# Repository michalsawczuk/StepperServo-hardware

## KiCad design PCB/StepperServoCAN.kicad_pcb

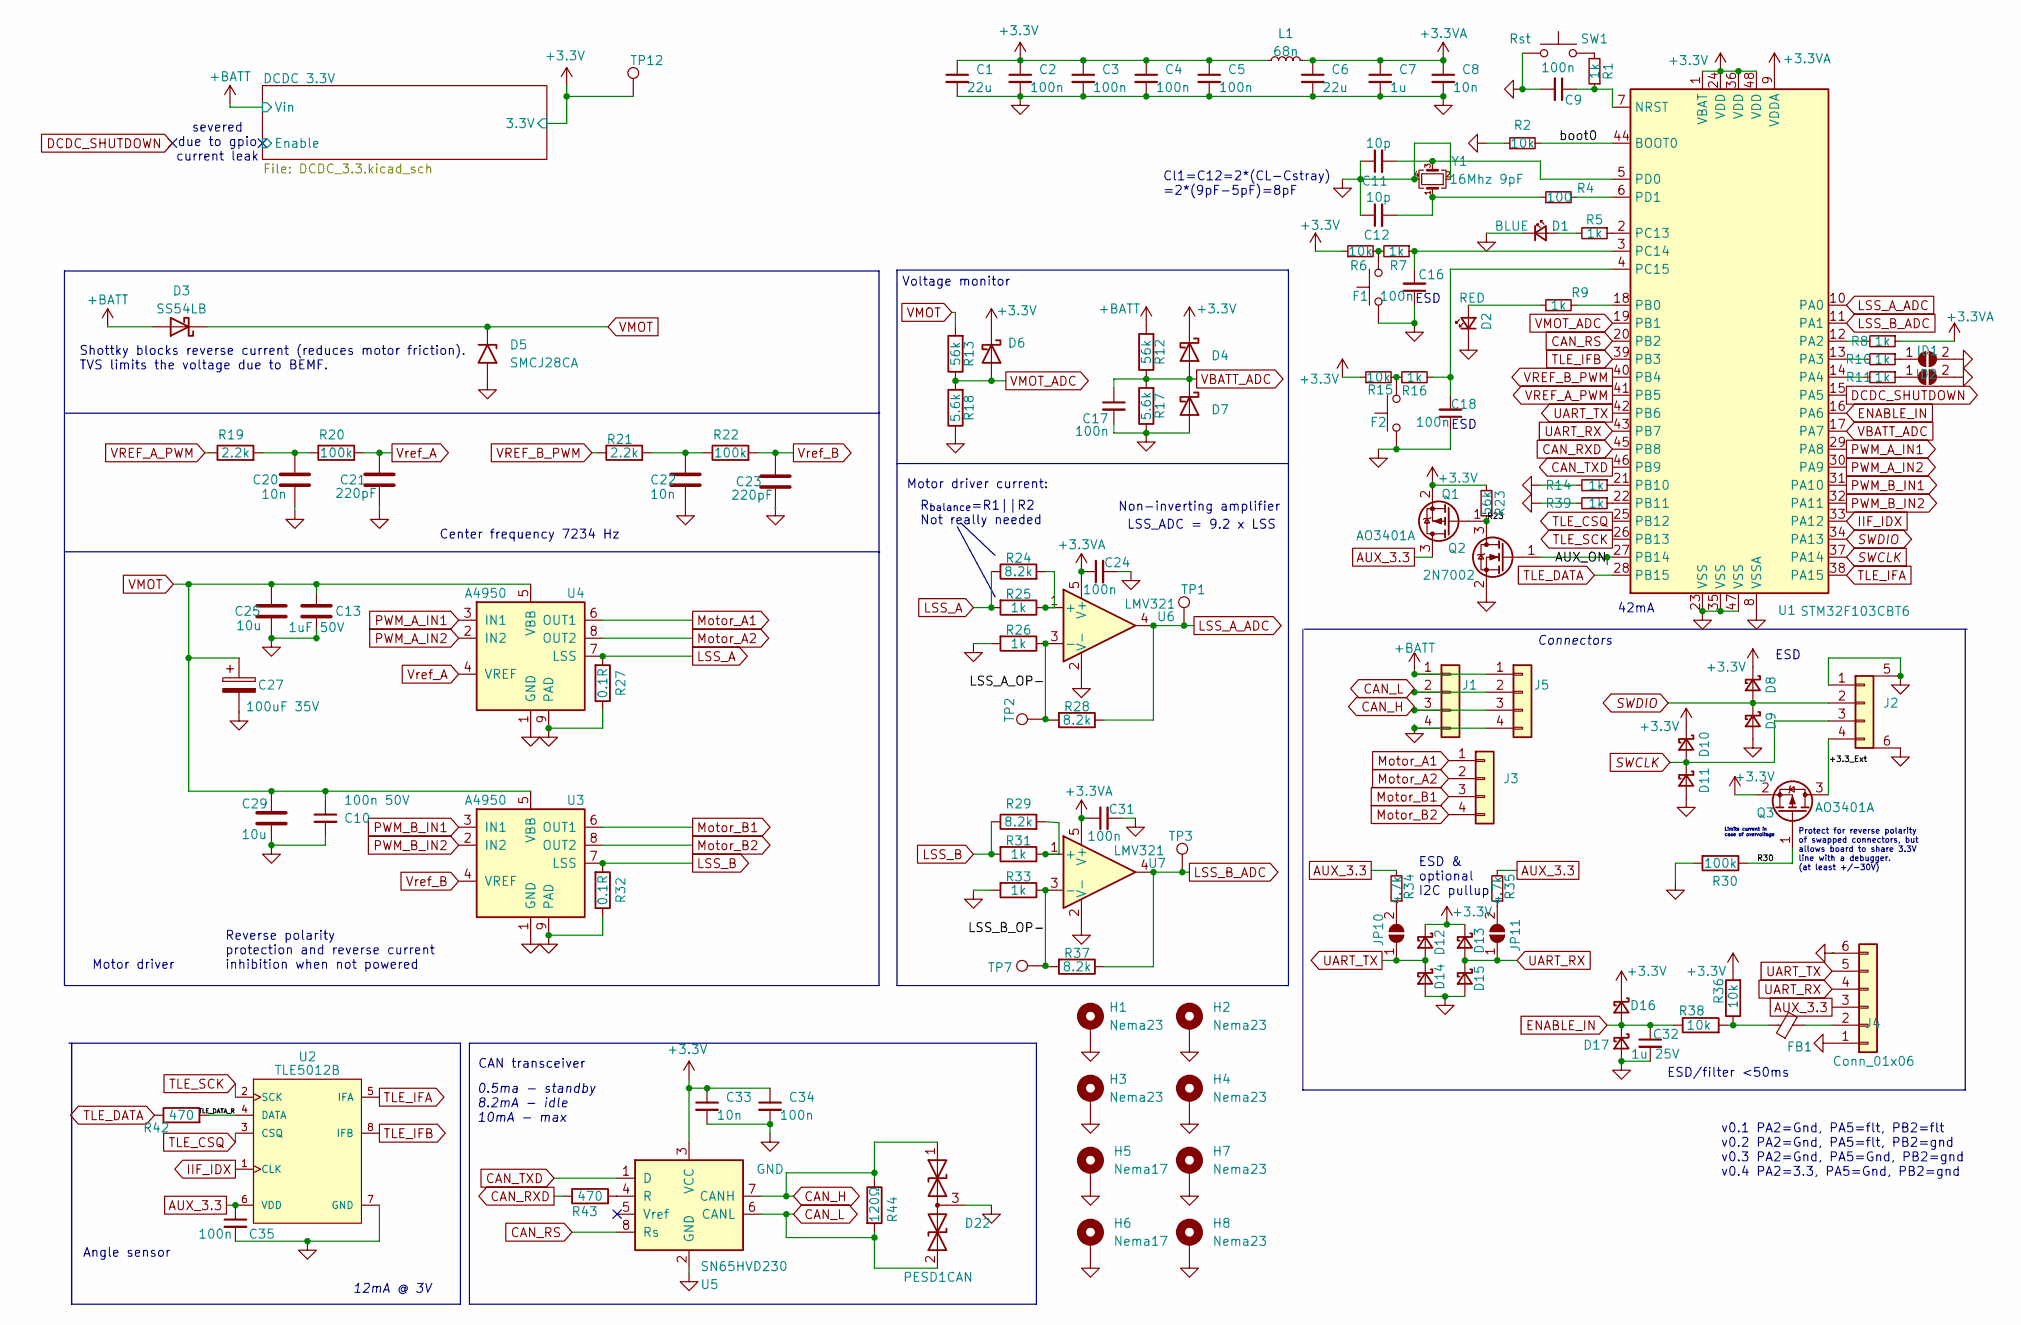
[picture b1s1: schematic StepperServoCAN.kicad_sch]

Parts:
C1, C6: 22u; C_0603_1608Metric; LCSC C59461
C2, C3, C4, C5, C9, C16, C17, C18, C24, C31, C34, C35: 100n; C_0402_1005Metric; LCSC C1525
C7: 1u; C_0402_1005Metric; LCSC C52923
C8, C20, C22, C33: 10n; C_0402_1005Metric; LCSC C15195
C10: 100n 50V; C_0402_1005Metric; LCSC C307331
C11, C12: 10p; C_0402_1005Metric; LCSC C32949
C13: 1uF 50V; C_0805_2012Metric; LCSC C28323
C21, C23: 220pF; C_0402_1005Metric; LCSC C1530
C25, C29: 10u; C_1206_3216Metric; LCSC C13585
C27: 100uF 35V; CP_Elec_6.3x5.7; LCSC C249982
C32: 1u 25V; C_0402_1005Metric; LCSC C52923
D1: BLUE; LED_0603_1608Metric; LCSC C2986058
D2: RED; LED_0603_1608Metric; LCSC C2286
D3: SS54LB; D_SMA; LCSC C7450527
D4, D6, D7, D8, D9, D10, D11, D12, D13, D14, D15, D16, D17: 1N5819WS; D_SOD-323; LCSC C191023
D5: SMCJ28CA; D_SMC; LCSC C19077606
D22: PESD1CAN; SOT-23; LCSC C152727
F1, F2: Fcn>; SW_SPST_TL3342; LCSC C318884
FB1: FerriteBead 200mA; L_0805_2012Metric; LCSC C1017
H1, H2, H3, H4, H7, H8: Nema23; MountingHole_3.2mm_M3_ISO14580_Pad_TopOnly
H5, H6: Nema17; MountingHole_3.2mm_M3_ISO14580_Pad_TopOnly
ID1, ID2: Jumper; SolderJumper-2_P1.3mm_Open_TrianglePad1.0x1.5mm
J1, J5: CAR; JST_XH_B4B-XH-A_1x04_P2.50mm_Vertical; LCSC C161861
J2: Debug; JST-S4B-XH-SM4-TB; LCSC C161861
J3: Motor; JST_XH_B4B-XH-A_1x04_P2.50mm_Vertical; LCSC C161861
J4: Conn_01x06; TerminalBlock_TE_282834-6_1x06_P2.54mm_Horizontal
JP10, JP11: I2C_PU; SolderJumper-2_P1.3mm_Open_RoundedPad1.0x1.5mm
L1: 68n; L_0603_1608Metric; LCSC C13415
Q1, Q3: AO3401A; SOT-23; LCSC C15127
Q2: 2N7002; SOT-23; LCSC C8545
R1, R5, R7, R8, R9, R10, R11, R14, R16, R25, R26, R31, R33, R39: 1k; R_0402_1005Metric; LCSC C11702
R2, R6, R15, R36, R38: 10k; R_0402_1005Metric; LCSC C25744
R4: 100; R_0402_1005Metric; LCSC C25076
R12, R13, R23: 56k; R_0402_1005Metric; LCSC C25796
R17, R18: 5.6k; R_0402_1005Metric; LCSC C25908
R19, R21: 2.2k; R_0402_1005Metric; LCSC C25879
R20, R22, R30: 100k; R_0402_1005Metric; LCSC C25741
R24, R28, R29, R37: 8.2k; R_0402_1005Metric; LCSC C25924
R27, R32: 0.1R; R_1206_3216Metric_Pad1.30x1.75mm_HandSolder; LCSC C201308
R34, R35: 4.7k; R_0805_2012Metric_Pad1.20x1.40mm_HandSolder; LCSC C17673
R42, R43: 470; R_0603_1608Metric; LCSC C23179
R44: 120Ω; R_1206_3216Metric_Pad1.30x1.75mm_HandSolder; LCSC C17909
SW1: Rst; SW_SPST_TL3342; LCSC C318884
TP1, TP2, TP3, TP7, TP12: Pad; TestPoint_Pad_D1.0mm
U1: STM32F103CBT6; LQFP-48_7x7mm_P0.5mm; LCSC C8734
U2: TLE5012B; Infineon-TLE5012-Level_A; LCSC C123083
U3, U4: A4950; SOIC-8-1EP_3.9x4.9mm_P1.27mm_EP2.41x3.3mm_ThermalVias; LCSC C82404
U5: SN65HVD230; SOIC-8_3.9x4.9mm_P1.27mm; LCSC C12084
U6, U7: LMV321; SOT-23-5; LCSC C7972
Y1: 16Mhz 9pF; Crystal_SMD_3225-4Pin_3.2x2.5mm; LCSC C13738

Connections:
+3.3V: C1.1, C2.1, C3.1, C4.1, C5.1, C33.1, C34.1, D4.1 (K), D6.1 (K), D8.1 (K), D10.1 (K), D12.1 (K), D13.1 (K), D16.1 (K), L1.1, Q1.2 (S), Q3.2 (S), R6.1, R15.1, R23.2, R36.2, TP12.1, U1.1 (VBAT), U1.24 (VDD), U1.36 (VDD), U1.48 (VDD), U5.3 (VCC); also elsewhere on the board
+3.3VA: C6.1, C7.1, C8.1, C24.1, C31.1, L1.2, R8.1, U1.9 (VDDA), U6.5 (V+), U7.5 (V+)
+BATT: D3.2 (A), J1.1, J5.1, R12.2; also elsewhere on the board
/+3.3_Ext: J2.4, Q3.3 (D)
/AUX_ON: Q2.1 (G), U1.27 (PB14)
/LSS_A_OP-: R26.1, R28.2, TP2.1, U6.3 (-)
/LSS_B_OP-: R33.1, R37.2, TP7.1, U7.3 (-)
/R23: Q1.1 (G), Q2.3 (D), R23.1
/R30: Q3.1 (G), R30.1
/TLE_DATA_R: R42.2, U2.4 (DATA)
/boot0: R2.2, U1.44 (BOOT0)
AUX_3.3: C35.1, J4.3, Q1.3 (D), R34.2, R35.2, U2.6 (VDD)
CAN_H: D22.1 (A1), J1.3, J5.3, R44.1, U5.7 (CANH)
CAN_L: D22.2 (A2), J1.2, J5.2, R44.2, U5.6 (CANL)
CAN_RS: U1.20 (PB2), U5.8 (Rs)
CAN_RXD: R43.1, U1.45 (PB8)
CAN_TXD: U1.46 (PB9), U5.1 (D)
DCDC_SHUTDOWN: U1.15 (PA5)
ENABLE_IN: C32.1, D16.2 (A), D17.1 (K), R38.1, U1.16 (PA6)
GND: C1.2, C2.2, C3.2, C4.2, C5.2, C6.2, C7.2, C8.2, C9.2, C10.2, C11.1, C12.1, C13.2, C16.1, C17.2, C18.1, C20.2, C21.2, C22.2, C23.2, C24.2, C25.2, C27.2, C29.2, C31.2, C32.2, C33.2, C34.2, C35.2, D1.1 (K), D2.1 (K), D5.2 (A2), D7.2 (A), D9.2 (A), D11.2 (A), D14.2 (A), D15.2 (A), D17.2 (A), D22.3 (common), F1.2, F2.2, H1.1, H2.1, H3.1, H4.1, H5.1, H6.1, H7.1, H8.1, ID1.2 (B), ID2.2 (B), J1.4, J2.1, J2.5 (Mount), J2.6 (Mount), J4.1, J4.6, J5.4, Q2.2 (S), R2.1, R14.2, R17.1, R18.1, R26.2, R27.1, R30.2, R32.1, R33.2, R39.2, SW1.1, U1.8 (VSSA), U1.23 (VSS), U1.35 (VSS), U1.47 (VSS), U2.7 (GND), U3.1 (GND), U3.9 (PAD), U4.1 (GND), U4.9 (PAD), U5.2 (GND), U6.2 (V-), U7.2 (V-), Y1.2, Y1.4; also elsewhere on the board
IIF_IDX: U1.33 (PA12), U2.1 (CLK)
LSS_A: R24.1, R25.2, R27.2, U4.7 (LSS)
LSS_A_ADC: R28.1, TP1.1, U1.10 (PA0), U6.4
LSS_B: R29.1, R31.2, R32.2, U3.7 (LSS)
LSS_B_ADC: R37.1, TP3.1, U1.11 (PA1), U7.4
Motor_A1: J3.1, U4.6 (OUT1)
Motor_A2: J3.2, U4.8 (OUT2)
Motor_B1: J3.3, U3.6 (OUT1)
Motor_B2: J3.4, U3.8 (OUT2)
unnamed: C12.2, R4.1, Y1.1
unnamed: C20.1, R19.2, R20.1
unnamed: C22.1, R21.2, R22.1
unnamed: D1.2 (A), R5.2
unnamed: D2.2 (A), R9.1
unnamed: F1.1, R6.2, R7.2
unnamed: F2.1, R15.2, R16.1
unnamed: FB1.1, R36.1, R38.2
unnamed: ID1.1 (A), R10.1
unnamed: ID2.1 (A), R11.1
unnamed: FB1.2, J4.2
unnamed: JP10.2 (B), R34.1
unnamed: JP11.2 (B), R35.1
unnamed: R1.2, SW1.2
unnamed: C9.1, R1.1, U1.7 (NRST)
unnamed: R8.2, U1.12 (PA2)
unnamed: R10.2, U1.13 (PA3)
unnamed: R11.2, U1.14 (PA4)
unnamed: R9.2, U1.18 (PB0)
unnamed: R14.1, U1.21 (PB10)
unnamed: R39.1, U1.22 (PB11)
unnamed: R5.1, U1.2 (PC13)
unnamed: C16.2, R7.1, U1.3 (PC14)
unnamed: C18.2, R16.2, U1.4 (PC15)
unnamed: C11.2, U1.5 (PD0), Y1.3
unnamed: R4.2, U1.6 (PD1)
unnamed: R43.2, U5.4 (R)
unnamed: R24.2, R25.1, U6.1 (+)
unnamed: R29.2, R31.1, U7.1 (+)
PWM_A_IN1: U1.29 (PA8), U4.3 (IN1)
PWM_A_IN2: U1.30 (PA9), U4.2 (IN2)
PWM_B_IN1: U1.31 (PA10), U3.3 (IN1)
PWM_B_IN2: U1.32 (PA11), U3.2 (IN2)
SWCLK: D10.2 (A), D11.1 (K), J2.3, U1.37 (PA14)
SWDIO: D8.2 (A), D9.1 (K), J2.2, U1.34 (PA13)
TLE_CSQ: U1.25 (PB12), U2.3 (CSQ)
TLE_DATA: R42.1, U1.28 (PB15)
TLE_IFA: U1.38 (PA15), U2.5 (IFA)
TLE_IFB: U1.39 (PB3), U2.8 (IFB)
TLE_SCK: U1.26 (PB13), U2.2 (SCK)
UART_RX: D13.2 (A), D15.1 (K), J4.4, JP11.1 (A), U1.43 (PB7)
UART_TX: D12.2 (A), D14.1 (K), J4.5, JP10.1 (A), U1.42 (PB6)
VBATT_ADC: C17.1, D4.2 (A), D7.1 (K), R12.1, R17.2, U1.17 (PA7)
VMOT: C10.1, C13.1, C25.1, C27.1, C29.1, D3.1 (K), D5.1 (A1), R13.2, U3.5 (VBB), U4.5 (VBB)
VMOT_ADC: D6.2 (A), R13.1, R18.2, U1.19 (PB1)
VREF_A_PWM: R19.1, U1.41 (PB5)
VREF_B_PWM: R21.1, U1.40 (PB4)
Vref_A: C21.1, R20.2, U4.4 (VREF)
Vref_B: C23.1, R22.2, U3.4 (VREF)

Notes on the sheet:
LSS_ADC = 9.2 x LSS
severed due to gpio current leak
42mA
ESD & optional I2C pullup
R_{balance}=R1||R2 Not really needed
v0.1 PA2=Gnd, PA5=flt, PB2=flt v0.2 PA2=Gnd, PA5=flt, PB2=gnd v0.3 PA2=Gnd, PA5=Gnd, PB2=gnd v0.4 PA2=3.3, PA5=Gnd, PB2=gnd
CAN transceiver
Non-inverting amplifier
Center frequency 7234 Hz
Angle sensor
Protect for reverse polarity of swapped connectors, but allows board to share 3.3V line with a debugger. (at least +/-30V)
ESD
Motor driver
ESD/filter <50ms
Shottky blocks reverse current (reduces motor friction). TVS limits the voltage due to BEMF.
Limits current in case of overvoltage
Connectors
12mA @ 3V
Reverse polarity protection and reverse current inhibition when not powered
Voltage monitor
0.5ma - standby 8.2mA - idle 10mA - max
Cl1=C12=2*(CL-Cstray) =2*(9pF-5pF)=8pF
Motor driver current:

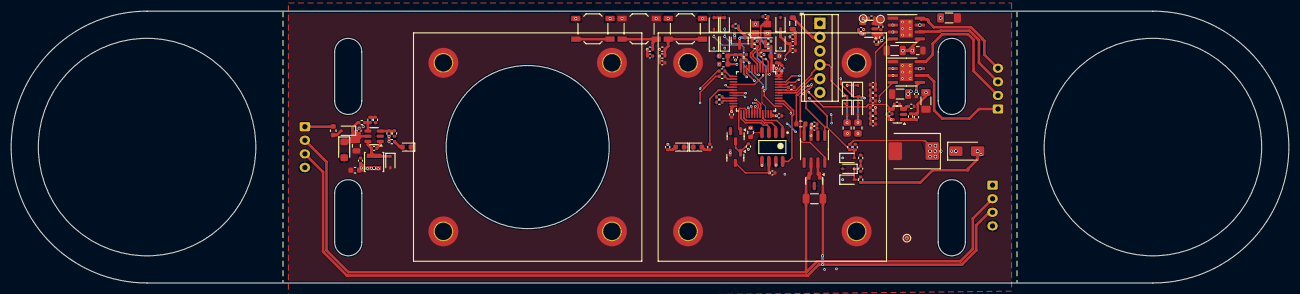
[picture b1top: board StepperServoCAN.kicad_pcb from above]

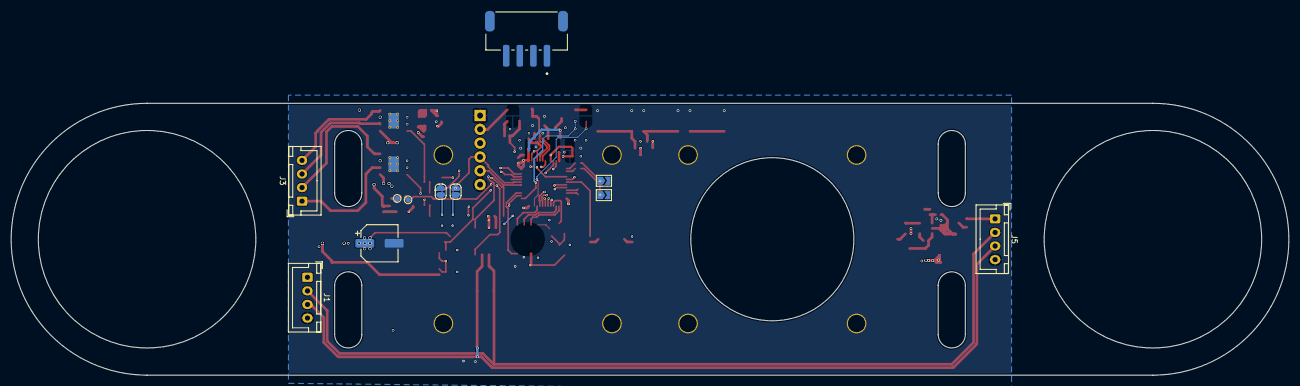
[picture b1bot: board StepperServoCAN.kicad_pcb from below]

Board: 4 copper layers, 235.0 x 50.0 mm, 144 parts (11 on the bottom side), 85 nets.

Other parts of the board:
C36, C38: 100n 50V; C_0402_1005Metric
C37: 10u; C_0805_2012Metric
C39: 100n; C_0402_1005Metric
C40: 22u; C_0603_1608Metric
D18: 1N4148WS; D_SOD-323
D19: SMF30CA; D_SMF
D20: 1N5819WS; D_SOD-323
D21: Yellow; LED_0603_1608Metric
FB2: FerriteBead; L_0603_1608Metric
L2: 100uH 250mA; L_Sunlord_SWPA3012S
R3: 0; R_0402_1005Metric
R45: 5.6k; R_0402_1005Metric
R46: 51k; R_0402_1005Metric
R47: 15k; R_0402_1005Metric
R48: 100k; R_0402_1005Metric
R49: 20k; R_0402_1005Metric
U11: LV2842XLVDDCR; TSOT-23-6

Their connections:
+3.3V: C39.1, C40.1, L2.2, R45.2, R46.2; also elsewhere on the board
+BATT: FB2.1; also elsewhere on the board
/DCDC 3.3V/BATT_Diode: C37.1, C38.1, D18.1 (K), D19.1 (A1), R48.2, U11.5 (VIN)
/DCDC 3.3V/Enable: R48.1, R49.2, U11.4 (EN)
GND: C37.2, C38.2, C39.2, C40.2, D19.2 (A2), D20.2 (A), D21.1 (K), R3.1, R47.1, U11.2 (GND); also elsewhere on the board
unnamed: D18.2 (A), FB2.2
unnamed: C36.2, D20.1 (K), L2.1, U11.6 (SW)
unnamed: D21.2 (A), R45.1
unnamed: R3.2, R49.1
unnamed: C36.1, U11.1 (BOOST)
unnamed: R46.1, R47.2, U11.3 (FB)

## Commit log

2025-08-30 outline etc.

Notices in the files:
PCB/StepperServoCAN.kicad_sch:
Licensed under CERN-OHL-S v2
